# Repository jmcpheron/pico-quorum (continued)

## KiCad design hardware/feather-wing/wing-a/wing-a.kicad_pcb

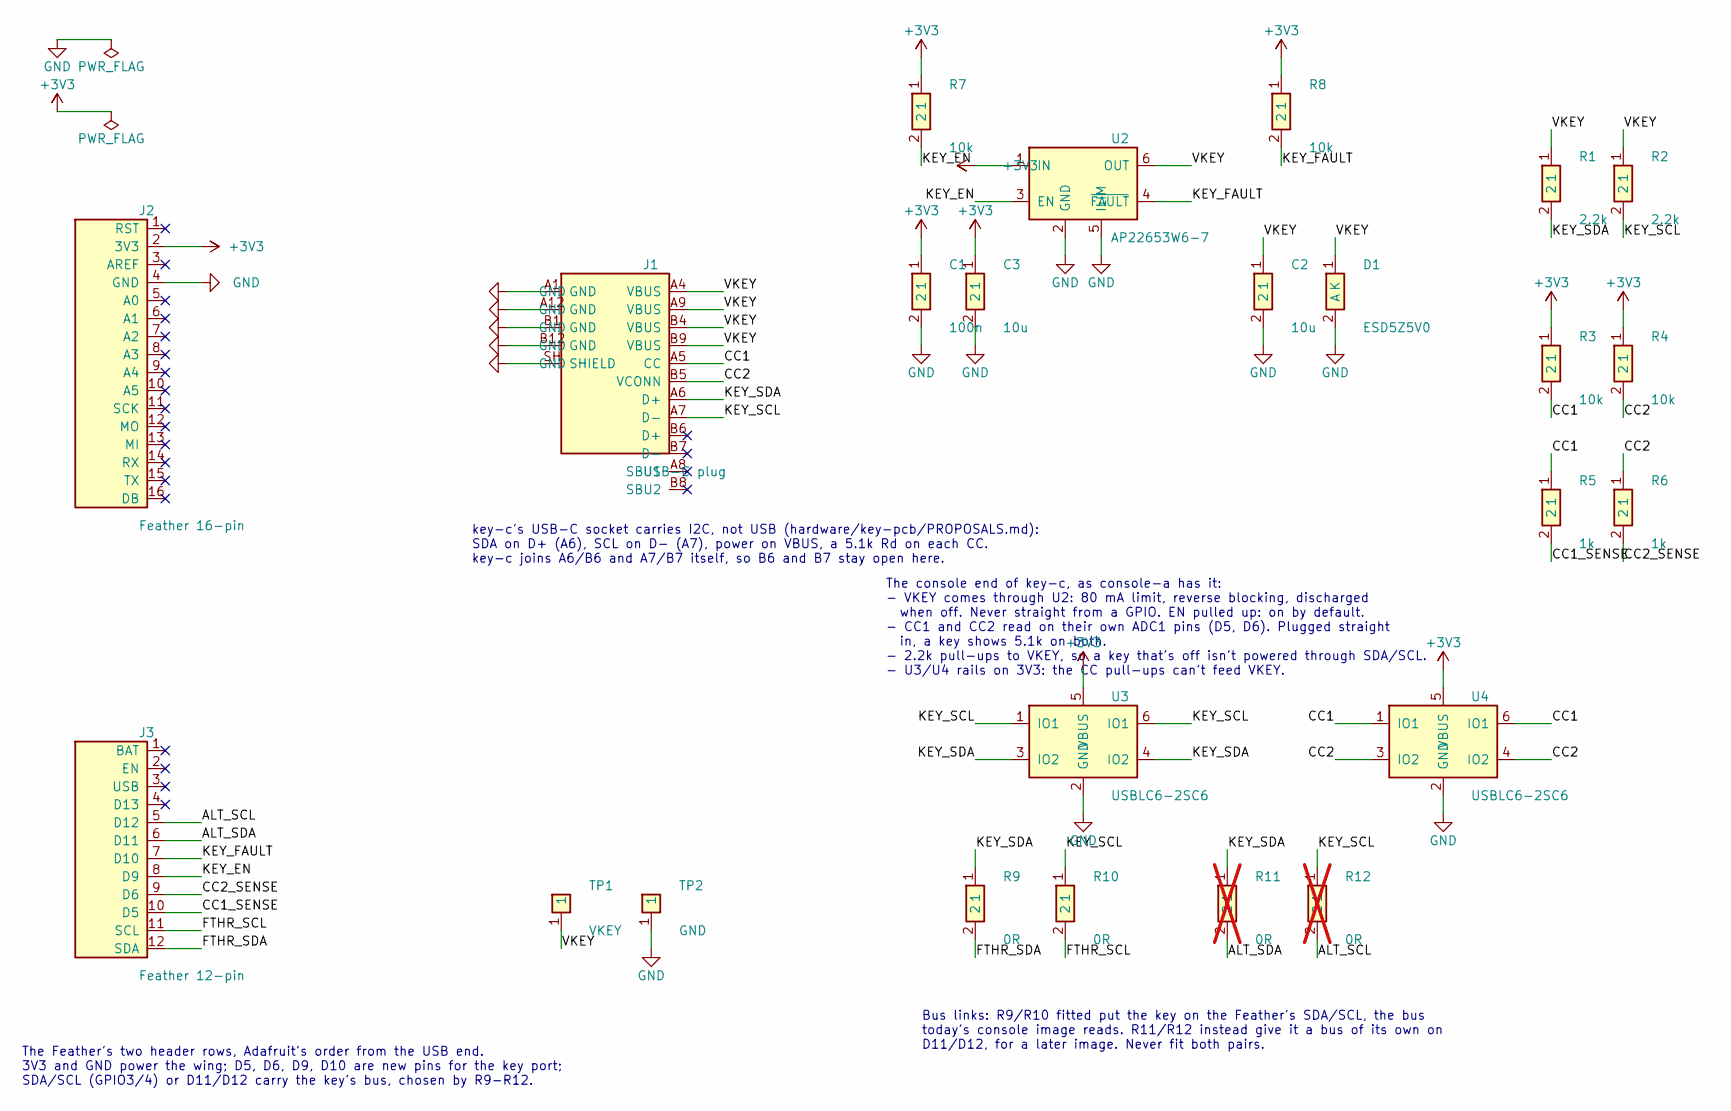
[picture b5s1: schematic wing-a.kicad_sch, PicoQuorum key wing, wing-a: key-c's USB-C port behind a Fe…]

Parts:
C1: 100n; C_0402; LCSC C1525
C2, C3: 10u; C_0603; LCSC C19702
D1: ESD5Z5V0; D_SOD-523; MPN ESD5Z5V0; LCSC C502546
J1: USB-C plug; USB_C_Plug_918-118A2021Y40002_Vertical; MPN 918-118A2021Y40002; LCSC C399939
J2: Feather 16-pin; Feather_Header_1x16
J3: Feather 12-pin; Feather_Header_1x12
R1, R2: 2.2k; R_0402; LCSC C25879
R3, R4, R7, R8: 10k; R_0402; LCSC C25744
R5, R6: 1k; R_0402; LCSC C11702
R9, R10: 0R; R_0402; LCSC C17168
R11, R12: 0R; R_0402; LCSC C17168; not fitted
TP1: VKEY; TestPad_1.5mm
TP2: GND; TestPad_1.5mm
U2: AP22653W6-7; SOT-23-6; MPN AP22653W6-7; LCSC C2158037
U3, U4: USBLC6-2SC6; SOT-23-6; MPN USBLC6-2SC6; LCSC C7519

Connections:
+3V3: C1.1, C3.1, J2.2 (3V3), R3.1, R4.1, R7.1, R8.1, U2.1 (IN), U3.5 (VBUS), U4.5 (VBUS)
/ALT_SCL: J3.5 (D12), R12.2
/ALT_SDA: J3.6 (D11), R11.2
/CC1: J1.A5 (CC), R3.2, R5.1, U4.1 (IO1), U4.6 (IO1)
/CC1_SENSE: J3.10 (D5), R5.2
/CC2: J1.B5 (VCONN), R4.2, R6.1, U4.3 (IO2), U4.4 (IO2)
/CC2_SENSE: J3.9 (D6), R6.2
/FTHR_SCL: J3.11 (SCL), R10.2
/FTHR_SDA: J3.12 (SDA), R9.2
/KEY_EN: J3.8 (D9), R7.2, U2.3 (EN)
/KEY_FAULT: J3.7 (D10), R8.2, U2.4 (~FAULT)
/KEY_LED: J1.A8 (SBU1), J1.B8 (SBU2); also elsewhere on the board
/KEY_SCL: J1.A7 (D-), R2.2, R10.1, R12.1, U3.1 (IO1), U3.6 (IO1)
/KEY_SDA: J1.A6 (D+), R1.2, R9.1, R11.1, U3.3 (IO2), U3.4 (IO2)
/LED_ALT: J2.5 (A0); also elsewhere on the board
/LED_D13: J3.4 (D13); also elsewhere on the board
/VKEY: C2.1, D1.1 (K), J1.A4 (VBUS), J1.A9 (VBUS), J1.B4 (VBUS), J1.B9 (VBUS), R1.1, R2.1, TP1.1, U2.6 (OUT)
GND: C1.2, C2.2, C3.2, D1.2 (A), J1.A1 (GND), J1.A12 (GND), J1.B1 (GND), J1.B12 (GND), J1.SH (SHIELD), J2.4 (GND), TP2.1, U2.2 (GND), U2.5 (ILIM), U3.2 (GND), U4.2 (GND); also elsewhere on the board

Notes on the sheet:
The Feather's two header rows, Adafruit's order from the USB end. 3V3 and GND power the wing; D5, D6, D9, D10 are new pins for the key port; SDA/SCL (GPIO3/4) or D11/D12 carry the key's bus, chosen by R9-R12.
key-c's USB-C socket carries I2C, not USB (hardware/key-pcb/PROPOSALS.md): SDA on D+ (A6), SCL on D- (A7), power on VBUS, a 5.1k Rd on each CC. key-c joins A6/B6 and A7/B7 itself, so B6 and B7 stay open here.
The console end of key-c, as console-a has it: - VKEY comes through U2: 80 mA limit, reverse blocking, discharged when off. Never straight from a GPIO. EN pulled up: on by default. - CC1 and CC2 read on their own ADC1 pins (D5, D6). Plugged straight in, a key shows 5.1k on both. - 2.2k pull-ups to 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
Bus links: R9/R10 fitted put the key on the Feather's SDA/SCL, the bus today's console image reads. R11/R12 instead give it a bus of its own on D11/D12, for a later image. Never fit both pairs.

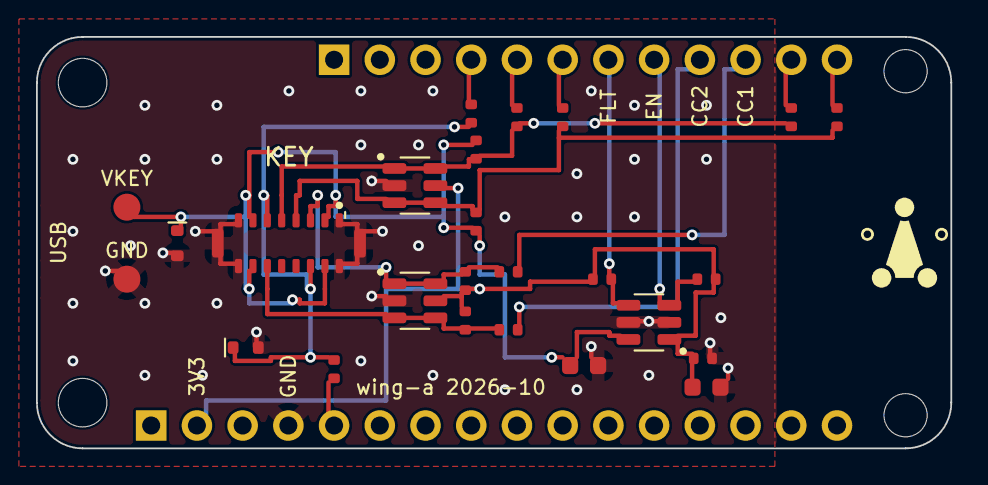
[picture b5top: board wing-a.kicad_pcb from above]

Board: 2 copper layers, 50.8 x 22.9 mm, 32 parts (0 on the bottom side), 18 nets.

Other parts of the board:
D3: ESD5Z5V0; D_SOD-523
H1, H2: M2.5; MountingHole_2.7mm
H3, H4: M2; MountingHole_2.4mm
LOGO1: PicoQuorum_Mark
R13, R14: 100; R_0402

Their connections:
/KEY_LED: D3.1, R13.1, R14.1; also elsewhere on the board
/LED_ALT: R14.2; also elsewhere on the board
/LED_D13: R13.2; also elsewhere on the board
GND: D3.2; also elsewhere on the board

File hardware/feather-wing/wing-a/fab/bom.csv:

Comment,Designator,Footprint,LCSC Part #
100n,C1,C_0402,C1525
10u,"C2,C3",C_0603,C19702
ESD5Z5V0,"D1,D3",D_SOD-523,C502546
USB-C plug,J1,USB_C_Plug_918-118A2021Y40002_Vertical,C399939
2.2k,"R1,R2",R_0402,C25879
100,R13,R_0402,C25076
10k,"R3,R4,R7,R8",R_0402,C25744
1k,"R5,R6",R_0402,C11702
0R,"R9,R10",R_0402,C17168
AP22653W6-7,U2,SOT-23-6,C2158037
USBLC6-2SC6,"U3,U4",SOT-23-6,C7519

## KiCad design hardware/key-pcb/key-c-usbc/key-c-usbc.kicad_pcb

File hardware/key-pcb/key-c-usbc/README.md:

# key-c: the USB-C key

> **P3, drawn 2026-10-23: P2 plus a green LED the console lights.** Not ordered. The files in this
> folder are P3.
>
> **P2: built and working.** 5 boards assembled by JLCPCB (order **W…1209** · PCBA **SMT…3772** ·
> $38.96). They read on the bench from 2026-10-16, and chip 3 is a Safe owner on the Feather. P2's
> files as ordered are in [`fab/P2/`](fab/P2/) and at commit `ac34fc55`.

## P3: the LED

| parts side |
|---|
|  |

P3 adds two parts, D1 and R3, and changes nothing else in the circuit:
- **D1, a green 0603 LED** (Everlight 19-217, C72043), beside U2, where the key shows when it
  stands in wing-a's plug.
- **R3, 470 Ω** (C25117), between the receptacle's SBU2 pin (B8) and D1. It comes first, so it
  limits whatever a plug puts on SBU. D1's cathode goes to ground.

**The console lights it.** wing-a joins its plug's A8 and B8 and drives them from D13 through
100 Ω ([feather-wing/README.md](../../archive/feather-wing/README.md)). D13 is the console's status LED
pin: today's image blinks it while a transaction waits for this key and keeps it on while Wi-Fi
is up (`led_tick` in `firmware/quorum.py`). So the key's LED does the same with no firmware change.
At 3.3 V that is about 1 mA, which this LED shows plainly; its datasheet rates it at 3.3 V,
20 mA.

**Only B8 is wired.** A8 sits between SDA's two receptacle pads, under SDA's via. The plug's A8 and
B8 are joined on the wing, so one of them meets B8 whichever way up the key goes in.

**Plugged in anywhere else, it stays dark.** A USB-C cable to a laptop carries no SBU on a USB 2.0
cable, and nothing on the key depends on SBU.

**Hot-swap: no change.** P2 already plugs and unplugs safely on wing-a:
- USB-C's ground and VBUS pins mate first and break last. GCT's connector drawings list them as
  "first" and the signal pins (CC, SBU, D+/D−) as "second". The HCTL receptacle's and the wing's
  plug's own drawings weren't checked for this.
- If a signal pin did touch first, U2's diodes carry what the wing's 2.2k pull-ups push into
  SDA/SCL on to the key's VCC: at most about 3 mA, set by the pull-ups.
- The key has 200 nF on VCC, and wing-a's switch limits the key's current to 80 mA.
- 11 plugs and unplugs on the bench reset nothing (log, 2026-10-16).

The rest of hot-swap is the console's: keep the key off until CC shows one, then turn it on. That
needs D5/D6 and D9 in the firmware, a new release
([feather-wing/README.md](../../archive/feather-wing/README.md#open)).

**Checked** (KiCad 10.0.6, `tools/keypcb check key-c-usbc`): ERC 0, DRC 0, 0 unconnected,
schematic parity clean. `gen_cd.py` was first checked to rebuild P2 exactly: every footprint, pad,
track and via the same.

**Ordering P3** is as P2 ([PROPOSALS.md](../PROPOSALS.md#ordering-key-c-at-jlcpcb)), plus: in the
placement preview, D1's cathode (pad 1, the bar in its silkscreen) faces the lanyard hole. D1 and
R3 are basic parts.

## P2 as ordered

| parts side | back |
|---|---|
|  |  |

These are KiCad renders of the ordered board, in the colours ordered: blue mask, white
silkscreen and silver lead-free HASL pads. KiCad has no 3D model of the HCTL receptacle, so the
connector shown is a GCT USB4105, a 16-pin receptacle of the same size and pad layout. The
renders come from a scratch copy of the board; the files below are untouched.

**3D models for CAD:** [`3d/key-c-P2.step`](3d/key-c-P2.step) is the assembled board, and
[`3d/key-c-P2-board-only.step`](3d/key-c-P2-board-only.step) is the bare board. They import
into Onshape as-is. Both come from the same scratch copy, with the same GCT stand-in connector at
J1's origin. The origin is the board centre, Z = 0 is the back face, and the USB-C end is at −Y.
The bare board is 1.51 mm thick (mask and copper not modelled). Units are mm.
To remake them: `kicad-cli pcb export step --user-origin 108x118mm`.

**Print mock-up:** [`3d/key-c-P2-print.step`](3d/key-c-P2-print.step) is a simplified version for
a 3D printer: one solid, same frame. The board, the chip bodies and the small parts are plain
blocks fused together. The USB-C receptacle is just its outer shell, with no tongue or contacts.
- The socket is 8.70 × 2.90 mm and 7.0 mm deep, so a real plug (8.25 × 2.40 mm) slides in with
  print clearance. A real-size plug was checked against it and doesn't touch.
- The shell walls are 0.8 mm (two perimeters), so the shell is 10.3 × 4.5 mm. The real one is
  8.94 × 3.26 mm, so the mock-up's shell is a little bigger.
- The board is 1.6 mm, as ordered. H1 is a 3 mm through hole.
- It prints flat, back face down, with no supports. The socket's round top bridges.
- The 0402 parts are 0.35–0.5 mm nubs and may not show on a coarse print.
- To remake it, or change the clearance or walls: `pip install cadquery`, then
  `python3 3d/print_mockup.py`.

**What it is:** an ATECC608C secure element (I2C, SOIC-8) behind a USB-C receptacle. The
receptacle is used as plain wires, not USB:
- D+ carries SDA, D− carries SCL and VBUS is key power.
- A 5.1 kΩ resistor on each CC pin tells the console a key is in.
- A USBLC6 ESD array sits between the connector and the chip.
- Four test pads on the back, and the Picoquorum mark.

The design is in [../PROPOSALS.md](../PROPOSALS.md), and the full order record is
[buildlog/2026-10-02-key-c-order.md](../../../buildlog/2026-10-02-key-c-order.md).

| | |
|---|---|
| Board | 16 × 36 mm, 2 layers, 1.6 mm, blue mask, white silkscreen, LeadFree HASL |
| Parts | U1 ATECC608C-SSHDA-T, U2 USBLC6-2SC6, J1 HCTL HC-TYPE-C-16P-01A, C1/C2 100 nF, R1/R2 5.1 kΩ |
| Files as ordered | commit `ac34fc55` on `key-pcb-learn`; Gerber zip SHA-256 `99a6dbb5…`, now in `fab/P2/` |
| Checks | ERC 0 · DRC 0 · unconnected 0 · parity clean (`tools/keypcb check key-c-usbc`) |

## Next

1. **Before plugging anything in:** build the console's end of the cable
   ([PROPOSALS.md](../PROPOSALS.md#the-console-end-of-key-c)):
   - a current-limited, reverse-blocking VBUS switch, enabled by GP6 and never GP6 directly
   - CC1 and CC2 sensed separately
   - 2.2 kΩ pull-ups to switched VBUS
2. **When the boards arrive:**
   - Look at each one under a loupe, and lightly sand the edges (they weren't deburred).
   - Meter it:
     - VCC to GND is not a short.
     - Each CC pin reads 5.1 kΩ to GND.
     - SDA and SCL aren't shorted to anything.
   - Check that the test pads read the same.
3. **First power-up on the bench:**
   - Only this key in the port.
   - Look for `0x60` in an I2C scan.
   - Read the chip's serial and configuration.
   - Lock nothing yet.
4. **Practise provisioning on a spare** before any key becomes a Safe owner.

## Log (newest first)

- **2026-10-23:** **P3 drawn**: P2 plus D1 (green LED) and R3 on SBU2, lit by the Feather's D13
  through wing-a. R1 moved left of U2 to make room. ERC/DRC clean. P2's fab files moved to
  `fab/P2/`.
- **2026-10-16:** **first power-up on the bench**, on an ESP32
  ([buildlog](../../../buildlog/BUILDLOG.md)). Nothing was locked.
  - The console's end wasn't built: key power straight from the 3.3 V rail, no CC sensing.
  - Nothing answered until IO21/IO22 had pull-ups. The ESP32's own (about 45 kΩ) were enough on
    the bench, up to 400 kHz with no errors.
  - `0x60` answered. Chip `0123e063db3354d7ee`: an ATECC608C, revision `00006005`, both zones
    unlocked, the factory table, SelfTest passes.
  - A second key, `0123147ac8c5b889ee`, also read. Plugged and unplugged 11 times between them,
    both ways round: each insertion read the right serial, and the ESP32 never reset.
- **2026-10-04:** **placement confirmed**, and the order is in production.
  - "Yes, please proceed to production."
  - The PCBA is at 13% (Data Finished) and fabrication at 0%.
  - Estimated finish: 2026-10-07 05:00.
- **2026-10-04:** STEP files of the ordered board added in `3d/`, for Onshape.
- **2026-10-04:** JLCPCB's parts-placement review arrived and was checked.
  - U1 and U2 have pin 1 at their triangles.
  - J1 faces the edge.
  - The 0402 parts aren't polarized.
  - It needs confirming in Order History within 72 hours.
- **2026-10-02:** status page and renders made.
- **2026-10-02:** checked the PCBA line's final parts list and the saved placement view.
  - All 5 parts are selected. C1 and C2 share the C1525 line, with 10 bought.
  - U1/U2 pin 1 sit at their triangles.
  - J1's pegs measure exactly on the peg holes.
- **2026-10-02:** the `cpl.csv` downloadable from the order is byte-identical to the upload. The
  placement edits live only in JLCPCB's system.
- **2026-10-02 17:14:** JLCPCB's production file arrived, was compared with the design, and was
  **confirmed**.
  - The input is byte-identical.
  - All 29 drills are at 0.000 mm offset.
  - Two 1.152 mm tooling holes were added, in plain ground pour.
  - Copper, silkscreen and mask show only normal fab changes.
  - Also checked by hand in GerbView.
- **2026-10-02 16:10:** **ordered**, W…1209, $38.96.
  - Economic PCBA, LeadFree HASL, Confirm Production file and Confirm Parts Placement.
  - Deburring didn't make it into the final order.
- **2026-10-02:** in JLCPCB's placement preview, U1 and U2 were rotated 90° (each pin-1 dot to its
  triangle) and J1 was nudged onto its pads.
- **2026-10-02:** **P2.** Redesigned after an outside review.
  - J1's footprint copy: outer ground pads pulled back to clear the peg holes, which removed the
    DRC exception.
  - U2 moved closer to J1, with C2 at its VBUS pin.
  - Four test pads on the back.
  - The board grew to 16 × 36 mm.
  - The review's console-side points went into PROPOSALS.md.
- **2026-10-02:** first upload, P1, 14 × 32 mm.
  - J1's yellow flag was only a $0.03 special-handling fee.
  - Economic assembly wasn't offered with ENIG but was with HASL. Standard would have forced a
    70 × 70 mm board.
- **2026-10-02:** the Picoquorum mark added to the back.
- **2026-10-02:** **P1** drawn, with key-d (pogo) beside it. The receptacle goes on the key rather
  than a plug: 16 pins on one side, cheap, assembled at JLCPCB.
- **2026-10-02:** rev A (the PCB is the plug) arrived on `main`. The spring-contact C1 concept was
  parked on `key-c1-concept`.

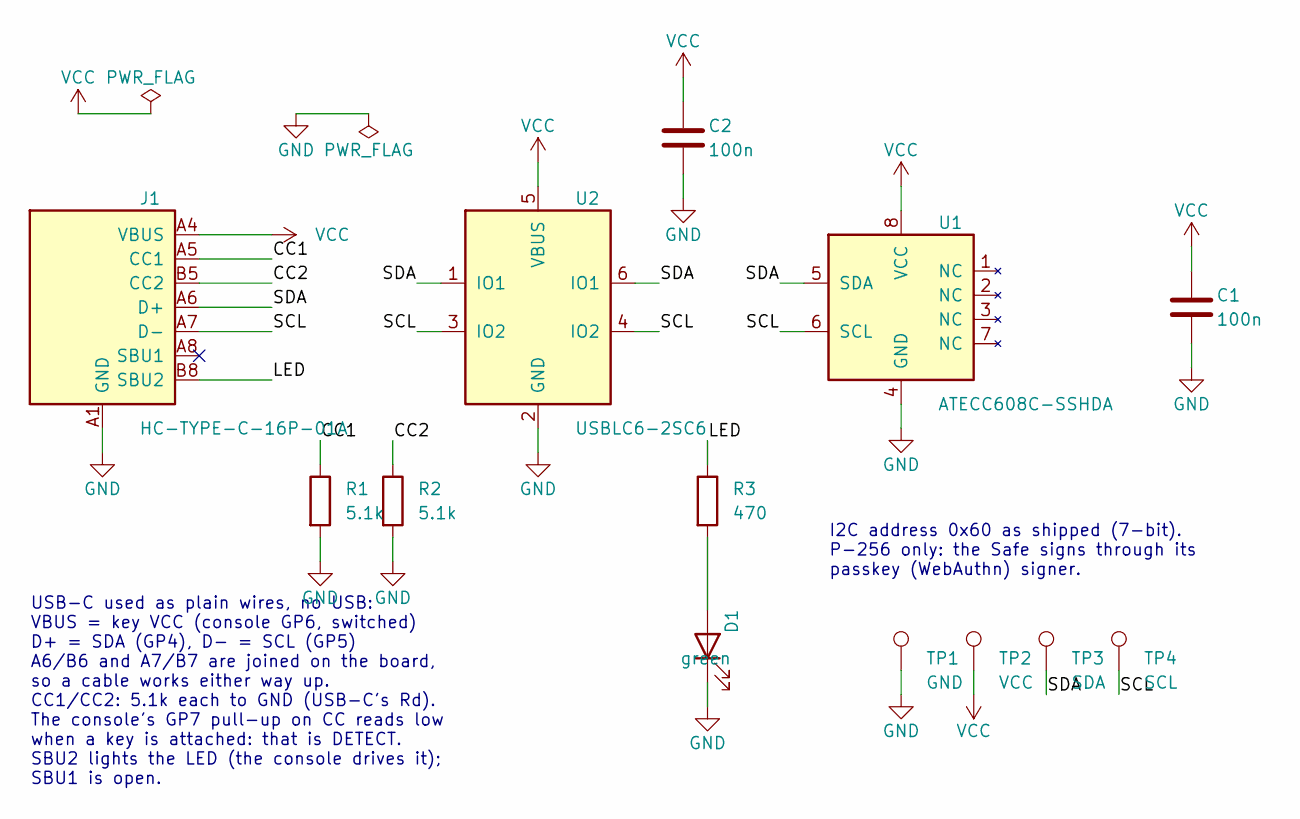
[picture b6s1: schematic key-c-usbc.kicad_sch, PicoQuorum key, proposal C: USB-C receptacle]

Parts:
C1, C2: 100n; C_0402_1005Metric; LCSC C1525
D1: green; LED_0603_1608Metric; MPN Everlight 19-217/GHC-YR1S2/3T; LCSC C72043
J1: HC-TYPE-C-16P-01A; USB_C_Receptacle_HCTL_HC-TYPE-C-16P-01A_PQ; MPN HC-TYPE-C-16P-01A; LCSC C2894897
R1, R2: 5.1k; R_0402_1005Metric; LCSC C25905
R3: 470; R_0402_1005Metric; LCSC C25117
TP1: GND; TestPoint_Pad_D1.5mm
TP2: VCC; TestPoint_Pad_D1.5mm
TP3: SDA; TestPoint_Pad_D1.5mm
TP4: SCL; TestPoint_Pad_D1.5mm
U1: ATECC608C-SSHDA; SOIC-8_3.9x4.9mm_P1.27mm; MPN ATECC608C-SSHDA-B; LCSC C28975195
U2: USBLC6-2SC6; SOT-23-6; MPN USBLC6-2SC6; LCSC C7519

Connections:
/CC1: J1.A5 (CC1), R1.1
/CC2: J1.B5 (CC2), R2.1
/LED: J1.B8 (SBU2), R3.1
/SCL: J1.A7 (D-), J1.B7 (D-), TP4.1, U1.6 (SCL), U2.3 (IO2), U2.4 (IO2)
/SDA: J1.A6 (D+), J1.B6 (D+), TP3.1, U1.5 (SDA), U2.1 (IO1), U2.6 (IO1)
GND: C1.2, C2.2, D1.1 (K), J1.A1 (GND), J1.A12 (GND), J1.B1 (GND), J1.B12 (GND), J1.SH (SHIELD), R1.2, R2.2, TP1.1, U1.4 (GND), U2.2 (GND)
unnamed: D1.2 (A), R3.2
VCC: C1.1, C2.1, J1.A4 (VBUS), J1.A9 (VBUS), J1.B4 (VBUS), J1.B9 (VBUS), TP2.1, U1.8 (VCC), U2.5 (VBUS)

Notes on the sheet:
I2C address 0x60 as shipped (7-bit). P-256 only: the Safe signs through its passkey (WebAuthn) signer.
USB-C used as plain wires, no USB: VBUS = key VCC (console GP6, switched) D+ = SDA (GP4), D- = SCL (GP5) A6/B6 and A7/B7 are joined on the board, so a cable works either way up. CC1/CC2: 5.1k each to GND (USB-C's Rd). The console's GP7 pull-up on CC reads low when a key is attached: that is DETECT.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

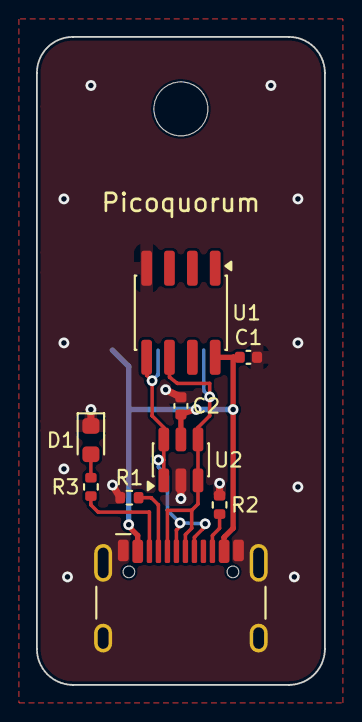
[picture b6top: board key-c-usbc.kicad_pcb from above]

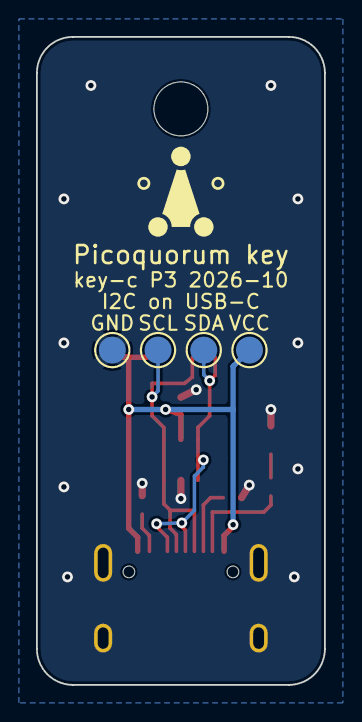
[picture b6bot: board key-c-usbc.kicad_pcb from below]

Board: 2 copper layers, 16.0 x 36.0 mm, 15 parts (5 on the bottom side), 8 nets.

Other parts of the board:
H1: Lanyard; MountingHole_3mm
LOGO1: PicoQuorum_Mark

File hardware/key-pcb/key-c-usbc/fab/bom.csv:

Comment,Designator,Footprint,LCSC Part #
100n,"C1,C2",C_0402_1005Metric,C1525
green,D1,LED_0603_1608Metric,C72043
HC-TYPE-C-16P-01A,J1,USB_C_Receptacle_HCTL_HC-TYPE-C-16P-01A_PQ,C2894897
5.1k,"R1,R2",R_0402_1005Metric,C25905
470,R3,R_0402_1005Metric,C25117
ATECC608C-SSHDA,U1,SOIC-8_3.9x4.9mm_P1.27mm,C28975195
USBLC6-2SC6,U2,SOT-23-6,C7519

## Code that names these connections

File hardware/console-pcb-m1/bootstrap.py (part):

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             'GP26', 'GP27', 'AGND', 'GP28', 'ADC_VREF', '3V3_OUT', '3V3_EN', 'GND', 'VSYS', 'VBUS']
pin_nets = {str(pin): 'BTN_' + label for label, gp, pin, x, y in BUTTONS}
pin_nets.update({str(pin): 'MCU_' + label for label, gp, pin in LCD})
pin_nets.update({'6': 'HOST_SDA', '7': 'HOST_SCL', '9': 'KEY_EN', '10': 'KEY_FAULT',
                 '31': 'ATTACH_A', '32': 'ATTACH_B', '30': 'RUN', '36': '+3V3',
                 'D1': 'SWCLK', 'D2': 'GND', 'D3': 'SWDIO'})
for i, name in enumerate(PIN_NAMES, 1):
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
